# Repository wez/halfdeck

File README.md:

# Half Deck - Mk 5

This is my fifth keyboard design.  This repo will be updated as I get around to
expanding the data here.

This is a split keyboard in two halves.  One half has a microcontroller that
implements USB and communicates with the other half using a two-wire bus
protocol known as I2C.

The other half has an IO expander component that is connected to the keyboard
matrix and that can be queried over I2C.

A TRRS (Tip-Ring-Ring-Sleeve) cable is used to connect the two halves; this is
a 4-wire cable that carries the power and I2C signals to the IO expander.

## Firmware

You can find example firmware for an atmega32u4 based Feather board here:
https://github.com/wez/qmk_firmware/tree/flutterby-rebased/keyboards/halfdeck

## Before you begin

The PCBs are double sided so that the same design can be used to build either
the RHS or the LHS of the keyboard.  Make sure you read through this doc and
understand where you're going to place the components before you cut or solder
anything, as it can be difficult to undo those actions.

If you are using a plate with your keyboard (eg: the top acrylic plate with the key
switch holes), keep in mind that you can't solder in any of the switches until
you have the plate as the switches effectively bolt the plate to the PCB.
If your plate material is thicker than ~1.6mm then it won't clip into the small
lugs on the switches and you may need to add some M3 spacers to raise the plate
up to the appropriate height; depending on how you flush you solder your diodes
that may not be required.

The labels for the controller and IO multiplexer are biased towards right
handed users, or rather, assume that the touchpad be located on the RHS.  If
you want to place it on the LHS you will need to swap the multiplexer and the
controller.  This should be straightforward, but will require attaching those
components upside-down.  Pay careful attention to the labels on the pins to
ensure that you have things placed correctly!

## Assembly - Left Hand

The top of the PCB faces up for the Left Hand.  You'll know you've got it facing the
correct direction because it has a graphic showing a left hand in the bottom left
corner, as well as some version information down there.

You will place the key switches on this side of the board for the left hand but
solder them in on the other side.

If you are right handed and also want to connect a touch pad, you will connect
the SX1509 on this half.

If you are left handed and also want to connect a touch pad, you will connect
the controller and the touch pad on this half.

### I2C Jumper configuration

On the top edge of the PCB there is a little notch where the TRRS connector
will be fitted.  To the right of that area is a pair of solder jumpers labelled
`JP1` and `JP2`.  These are present to allow setting up the same PCB for either
left or right handed usage and control which pins of the TRRS connector are
connected to the power and ground lines.

Each jumper consists of three rectangles.  The middle of the three needs to
be bridged to *either* the left or the right pad using either excess solder
or a short section snipped off of one of the diode legs.  Controlling excess
solder can be difficult, so I would suggest using a diode leg trimmed to size
if you're not confident, or you don't have a solder sucker on hand to undo.

* `JP1` must be bridged to `3V3`
* `JP2` must be bridged to `GND`

It's not the end of the world if you mix this up, so long as each jumper either
goes to `GND` or `3V3`.  They must not both be set to the same thing or you
risk damaging your electronics.

This image shows the jumpers for the LHS:

## Assembly - Right Hand

The bottom of the PCB faces up for the Right Hand.  You'll see a graphic
showing a right hand in the bottom right corner of the PCB.

You will place the key switches on this side of the board for the right hand
but solder them in on the other side.

If you are right handed and also want to connect a touch pad, you will connect
the controller and the touch pad on this half.

If you are left handed and also want to connect a touch pad, you will connect
the SX1509 on this half.

### I2C Jumper configuration

Similar to the note on the Left Hand, but the Right Hand absolutely must have
the opposite settings to the Left Hand!

* `JP1` must be bridged to `GND`
* `JP2` must be bridged to `3V3`

While the PCB is mostly reversible, the jumper blocks are only present on
one side of the board, so you need to flip it over to configure them.

This image shows the jumpers for the HHS:

## Errata

The first batch of these boards have a minor issue with the `SCL` line; due to
a typo it isn't actually connected to the TRRS jack.  You will need to bridge
the misnamed `SDL` pads to the `SCL` pads on each side.

### Patching the RHS

### Patching the LHS

## Recommended Order of Assembly

1. Diodes
2. The TRRS connectors
3. Jumpers (I2C and the Errata section above)
4. Header strip for the controller/expander
5. Key switches
6. Touchpad

## Diodes

The diodes are directional; they allow current to flow in a single direction.
Their purpose in the circuit is to prevent ghosting.  If you attach one in
the wrong direction it can be hard to debug and isolate if you don't have
a multimeter, so take care to make sure you've placed them correctly.

The diodes have a black line at one end.  The black line must be aligned with
the thick white line in the diode outline on the PCB.  The solder pad on that
side is square, which is another visual cue; think *black, thick, square*.

Bend the legs of the diode so that you form a slender `n` shape, with the diode
body at the top of the `n`.  The goal is to have the diode body lay flush against
the PCB within the outline on the pcb, so you want the legs to bend and fit the
holes at either end of the outline.

I'd suggest taking your time with the first one and perhaps solder that one
before placing the rest to make sure you understand how it will fit.  Make
sure that you have it oriented correctly before soldering!

To solder the diodes, the technique is important.  You're placing the diodes
on the side of the board facing up but you need to solder them on the back side
of the board.  I bend the legs to form a `V` shape to keep the diodes in place
when you flip the board over:

Once you've placed the diodes, check again to make sure that you have them
facing the right direction (*black, thick, square*) and solder them in.  You
want enough solder that you fill the hole with a nice shiny blob, and you want
it to be very slightly convex.

Be careful with the diode legs: you can easily prick yourself on the legs and
the human reflex to suddenly move away from the prick can be dangerous if one
of your hands is holding a hot soldering iron!

After soldering, double check the orientation of the diodes again: it's not
super easy to correct at this point, but it will get much harder if you
discover a problem later because the next step is to snip off the diode legs.

Use your angle/flush cutters for this; lay the edge of the cutters flush with
the board and snip off the leg where it comes through the hole.  Ideally you
want to trim it such that you're just left with a small convex mound of solder
around the hole.  I recommend holding the leg with one hand while you snip; the
picture below doesn't show this because I was holding the camera to take the
picture.  The reason for holding the leg while snipping is that it can jump off
your work surface and land on the floor.  If you're not diligent at tracking
and picking up the legs from the floor, it is easy for someone to stub/stab a
toe with a diode leg.  While they're not super sharp, they're small enough that
they can jab in a few millimeters and draw blood.

## TRRS Connectors

Attaching these is pretty straightforward; look for the little notch in the PCB
near the I2C jumpers.  The notch makes room for the circular opening in the
connector.  Place the legs of the component through the holes and solder on the
other side.

If you are using a plate with your keyboard, check to see whether you have enough
clearance to mount the connector on the switch side of the plate.  If you
have an acrylic plate than I suspect that there won't be enough clearance.
If you're using a 1.6mm plate then it looks like it might just fit.

In the pictures in this guide, I built without a plate and placed the connectors
on the top side of the PCB.

## Header Strip for Controller and Expander

I recommend using some header strip to mount these components.  The controller
comes with appropriately sized strip but you'll need to obtain some more header
to mount the IO expander.

Similar consideration as the TRRS connector: make sure that you have enough
clearance to place the components and your plate if you're using a plate.  You
may need to mount the components on the opposite side of the board to
accomodate your plate.   Note that you can also [buy short header
strip](https://www.adafruit.com/product/3002) for lower profile builds.

This image shows the header strip placement for the IO Expander:

When soldering the header be prepared: `GND` is attached to a larger ground
plane fill in that area of the board; there's large region of copper under the
surface coating and that means that it will soak up the heat from your iron and
be more difficult/take longer to solder than the surrounding pins. You may
notice that the PCB in that region is noticeably much hotter.  This is fine.

## Key Switches

These should also be pretty simple to place, especially if you ordered PCB
mounted switches.  The PCB mounted switches have a couple of extra legs to
ensure that the switch is correctly aligned in the PCB.  If you have plate
mounted switches, those lugs are not present because the plate is supposed to
orient and align the switches.

If you're using plate mounted switches on the PCB and are not using a plate
you will need to take extra care to ensure that the switches mount square
and consistently, otherwise your keycaps will be misaligned.

Press the key switches into the mounting holes; make sure that the metal legs
of the switch poke through the other side.  If you don't see a leg poking
through it means that the leg is most likely folded flat; remove the switch and
straighten the leg and try again.

Make sure that the switches are pushed in snugly and that the switches are
flush with the PCB, otherwise your keycaps will be misaligned.  You may hear or
feel a click when the switch is well placed.

I tend to place all of the switches at once, then flip the board over and
solder them in.  Before you solder, make sure that none of the switches shifted
during the flip.  In my test build the tolerance on the hole was good and the
switches were held in just fine, but depending on your switches you may find
that one or two of them are a little loose and need to be re-seated.

## Touchpad

I tried two different touchpad models.  The one I'm most happy with is the
Azoteq TPS43-201A-S, which is a 43mm approximately-square touchpad which
connects to the I2C bus on this keyboard.  When I designed the board I
though I was going to use a different touchpad that was connected via SPI,
so the mounting area on the board breaks out the SPI pins but not the I2C
pins.  That means that connecting the touchpad requires a couple of bridging
wires to connect across the backside of the pcb.

The touchpad is shipped with a removable 3M adhesive pad on the touch surface;
**keep this attached to the touchpad** (well, you can peel back a corner and
take a peek at the sensor grid if you like).  The purpose of this is to ensure
that you have no air gap between the capacitive touch grid on the touchpad
surface and the touch surface.  The 3M label makes a reasonable touch surface,
but you may want to consider placing your own more permanent and aestheticly
pleasing surface in its place.  The datasheet recommends a surface that is no
more than 3mm thick, and it should be something that doesn't interfere with the
capacitive field.

### Touchpad Wiring

Prepare your bridging wires; you'll need 3 that are long and two that are relatively
short.  You'll want to give yourself a little slack but not so much that
the wires crowd out the underside of your board.

Here's a picture of the wiring on the reverse of the PCB so that you can
visualize this a little better; the slack allows popping off the case in
the event that you need to get inside the board and clean it.

The touchpad itself provides solderable pads that are just perfect for
our needs:

The pads are connected to the PCB via the briding wires:

| Touchpad | PCB |
| -------- | --- |
| SDA      | SDA - on the header block at the top of the board |
| SCL      | SCL - on the first rev of the PCB this is mislabeled as SDL on the header block at the top of the board |
| 3V3      | 3V3 - in the header block in the circle at the bottom of the board |
| GND      | GND - in the header block in the circle at the bottom of the board |
| RST      | Not connected |
| RDY      | ~INT - the interrupt pin behind the microcontroller |

### Orientation of the touchpad

The top edge of the touchpad has a small notch.  When the touchpad is placed
on the board, the solder pads for the connections listed in the table above
will be in the bottom right of the touchpad if you look down from the top
surface of the touch pad.

While you're soldering you'll have it facing up the other way and so those pads
will be in the bottom left of the underside of the touchpad.

### Mounting the touchpad

I've only made this work when integrating with the 3D printed flavor of the case.
You'll need the [touchpad_stand](case/touchpad_stand.stl) to raise the pad up to
the level of the case.  There is an open side in the touchpad stand that is intended
to allow your wiring to pass through; the idea is that you don't want to solder your
wires into the stand as you won't be able to remove it without de-soldering.

## Case

In the [case](case) directory you'll find a number of files to use for the case.  You
have a couple of options:

### 2D laser cut sandwich style case

This is the simplest case design, but because it is 2D doesn't have a story for (literally)
supporting the touchpad.  There are no sides to the case and the idea is that
you assemble it using some M3 standoffs/spacers and nuts and bolts.  There are a number
of SVG files in the repo that can be used to assemble a case.  For example, you can
take [this one](case/half-deck-case-bottom-and-switch-plate-no-touch-pad-ponoko-p2.svg)
to [Ponoko](https://www.ponoko.com/) and select you preferred color of acrylic P2 material.

### 3D printed case (work in progress)

> Pictured above: a debug version of the case with partially exposed controller.
> The case files below are fully enclosed but I don't have a real print of that
> to show at this time.

This one is your best option when using a touchpad.  There are a couple of parts to print in
the current iteration.  These are for a right handed build including a touchpad.  You can
mirror the parts if you want a left handed build with a touchpad, or just mirror the left
half if you want a right half with no touchpad:

 * [left half](case/left-case.stl)
 * [right_half](case/right-case.stl)
 * [touchpad_stand](case/touchpad_stand.stl)
 * Currently missing: bottom cover.  It's not strictly needed as the case has a lip
   with sufficient clearance, but you can extrude [case-bottom.svg](case/case-bottom.svg)
   and print that or just laser cut it from some other material if you really need
   something.

You'll need some M3 bolts to attach the PCB to the case and something like these
[heat-set embedment nuts](https://www.amazon.com/gp/product/B01IYWTCWW)
to provide threads that you can screw the bolts into.  Check out 
[this page](https://www.3dhubs.com/knowledge-base/how-assemble-3d-printed-parts-threaded-fasteners)
for more information.

If you don't have a 3D printer you can upload these files to somewhere like
[3D Hubs](https://www.3dhubs.com/) and have them printed for you at a cost of
around $50 for one set, plus shipping.

If you do have a 3D printer but it isn't large enough to print these models, you'll
find a set of `sliced_case` files in this repo that are divided into quarters that
are printable in a printer with a 140 cubic mm volume.  These are cut in such a way
that the pieces lock together when mounted on the PCB.

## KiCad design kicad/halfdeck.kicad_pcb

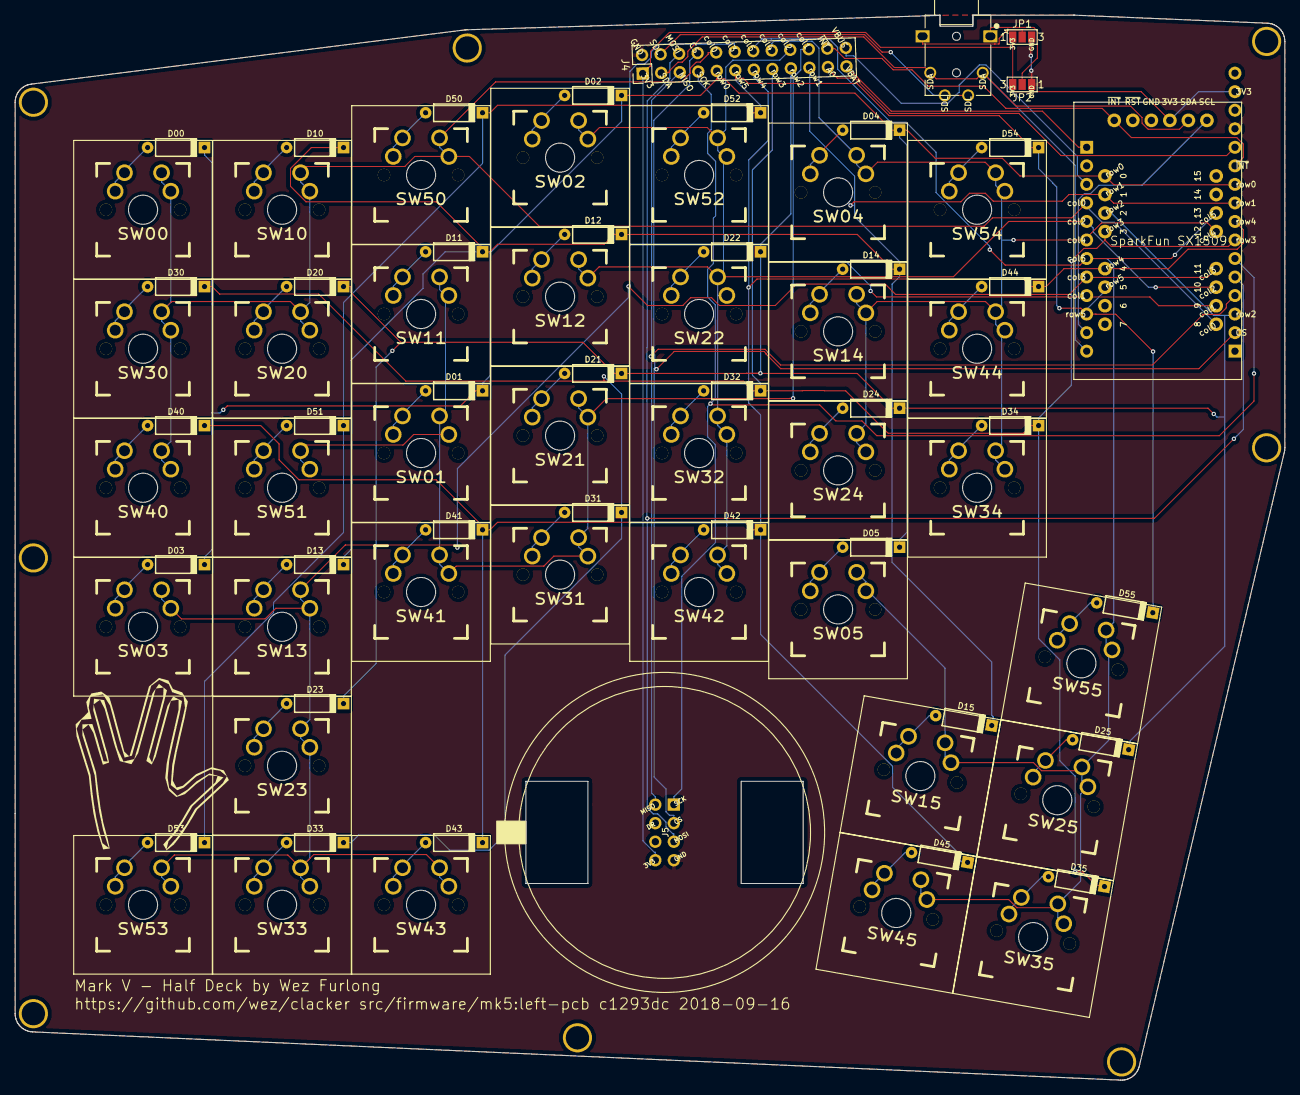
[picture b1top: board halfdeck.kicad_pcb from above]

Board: 2 copper layers, 174.0 x 145.9 mm, 89 parts (1 on the bottom side), 63 nets.

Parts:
CP0: VAL**; CP0
CP1: VAL**; CP1
CP2: VAL**; CP2
CP3: VAL**; CP3
CP4: VAL**; CP4
CP5: VAL**; CP5
CP6: VAL**; CP6
CP7: VAL**; CP7
D00: D; D00
D01: D; D01
D02: D; D02
D03: D; D03
D04: D; D04
D05: D; D05
D10: D; D10
D11: D; D11
D12: D; D12
D13: D; D13
D14: D; D14
D15: D; D15
D20: D; D20
D21: D; D21
D22: D; D22
D23: D; D23
D24: D; D24
D25: D; D25
D30: D; D30
D31: D; D31
D32: D; D32
D33: D; D33
D34: D; D34
D35: D; D35
D40: D; D40
D41: D; D41
D42: D; D42
D43: D; D43
D44: D; D44
D45: D; D45
D50: D; D50
D51: D; D51
D52: D; D52
D53: D; D53
D54: D; D54
D55: D; D55
J1: VAL**; J1
J4: Pin_Header_Straight_2x12_Pitch2.54mm; J4
J5: VAL**; J5
JP1: SolderJumper-3_P1.3mm_Open_Pad1.0x1.5mm_NumberLab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; JP1
JP2: SolderJumper-3_P1.3mm_Open_Pad1.0x1.5mm_NumberLab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; JP2
SW00: SW00
SW01: SW01
SW02: SW02
SW03: SW03
SW04: SW04
SW05: SW05
SW10: SW10
SW11: SW11
SW12: SW12
SW13: SW13
SW14: SW14
SW15: SW15
SW20: SW20
SW21: SW21
SW22: SW22
SW23: SW23
SW24: SW24
SW25: SW25
SW30: SW30
SW31: SW31
SW32: SW32
SW33: SW33
SW34: SW34
SW35: SW35
SW40: SW40
SW41: SW41
SW42: SW42
SW43: SW43
SW44: SW44
SW45: SW45
SW50: SW50
SW51: SW51
SW52: SW52
SW53: SW53
SW54: SW54
SW55: SW55
U1: FEATHER; U1
U2: SparkFun SX1509; U2
X9: G***; X9
X10: G***; X10

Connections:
3V3: J4.1, J5.8, JP1.1, JP2.3, U1.+3V3, U2.3V3
A0: J4.21, U1.A0
CS: J4.8, J5.3, U1.D1
GND: J4.2, J5.7, JP1.3, JP2.1, U1.GND, U2.GND
MISO: J4.5, J5.2, U1.MISO
MOSI: J4.6, J5.5, U1.MOSI
unnamed: J1.R2, JP1.2
unnamed: J1.S, JP2.2
unnamed: D00.2, SW00.2, SW00.2a
unnamed: D01.2, SW01.2, SW01.2a
unnamed: D02.2, SW02.2, SW02.2a
unnamed: D03.2, SW03.2, SW03.2a
unnamed: D04.2, SW04.2, SW04.2a
unnamed: D05.2, SW05.2, SW05.2a
unnamed: D10.2, SW10.2, SW10.2a
unnamed: D11.2, SW11.2, SW11.2a
unnamed: D12.2, SW12.2, SW12.2a
unnamed: D13.2, SW13.2, SW13.2a
unnamed: D14.2, SW14.2, SW14.2a
unnamed: D15.2, SW15.2, SW15.2a
unnamed: D20.2, SW20.2, SW20.2a
unnamed: D21.2, SW21.2, SW21.2a
unnamed: D22.2, SW22.2, SW22.2a
unnamed: D23.2, SW23.2, SW23.2a
unnamed: D24.2, SW24.2, SW24.2a
unnamed: D25.2, SW25.2, SW25.2a
unnamed: D30.2, SW30.2, SW30.2a
unnamed: D31.2, SW31.2, SW31.2a
unnamed: D32.2, SW32.2, SW32.2a
unnamed: D33.2, SW33.2, SW33.2a
unnamed: D34.2, SW34.2, SW34.2a
unnamed: D35.2, SW35.2, SW35.2a
unnamed: D40.2, SW40.2, SW40.2a
unnamed: D41.2, SW41.2, SW41.2a
unnamed: D42.2, SW42.2, SW42.2a
unnamed: D43.2, SW43.2, SW43.2a
unnamed: D44.2, SW44.2, SW44.2a
unnamed: D45.2, SW45.2, SW45.2a
unnamed: D50.2, SW50.2, SW50.2a
unnamed: D51.2, SW51.2, SW51.2a
unnamed: D52.2, SW52.2, SW52.2a
unnamed: D53.2, SW53.2, SW53.2a
unnamed: D54.2, SW54.2, SW54.2a
unnamed: D55.2, SW55.2, SW55.2a
SCK: J4.7, J5.1, U1.SCK
SCL: U1.SCL, U2.SCL
SDA: J1.T, J1.Talt, J4.3, U1.SDA, U2.SDA
SDL: J1.R1, J1.R1alt, J4.4
VBAT: J4.23, U1.VBAT
VBUS: J4.24, U1.VBUS
col0: J4.10, SW00.1, SW00.1a, SW10.1, SW10.1a, SW20.1, SW20.1a, SW30.1, SW30.1a, SW40.1, SW40.1a, SW50.1, SW50.1a, U1.D13, U2.8
col1: J4.20, SW01.1, SW01.1a, SW11.1, SW11.1a, SW21.1, SW21.1a, SW31.1, SW31.1a, SW41.1, SW41.1a, SW51.1, SW51.1a, U1.D6, U2.9
col2: J4.18, SW02.1, SW02.1a, SW12.1, SW12.1a, SW22.1, SW22.1a, SW32.1, SW32.1a, SW42.1, SW42.1a, SW52.1, SW52.1a, U1.D12, U2.10
col3: J4.12, SW03.1, SW03.1a, SW13.1, SW13.1a, SW23.1, SW23.1a, SW33.1, SW33.1a, SW43.1, SW43.1a, SW53.1, SW53.1a, U1.D9, U2.11
col4: J4.16, SW04.1, SW04.1a, SW14.1, SW14.1a, SW24.1, SW24.1a, SW34.1, SW34.1a, SW44.1, SW44.1a, SW54.1, SW54.1a, U1.D11, U2.12
col5: J4.14, SW05.1, SW05.1a, SW15.1, SW15.1a, SW25.1, SW25.1a, SW35.1, SW35.1a, SW45.1, SW45.1a, SW55.1, SW55.1a, U1.D10, U2.13
row0: D00.1, D01.1, D02.1, D03.1, D04.1, D05.1, J4.9, U1.A2, U2.0
row1: D10.1, D11.1, D12.1, D13.1, D14.1, D15.1, J4.19, U1.A3, U2.1
row2: D20.1, D21.1, D22.1, D23.1, D24.1, D25.1, J4.17, U1.D0, U2.2
row3: D30.1, D31.1, D32.1, D33.1, D34.1, D35.1, J4.15, U1.A5, U2.3
row4: D40.1, D41.1, D42.1, D43.1, D44.1, D45.1, J4.13, U1.A4, U2.4
row5: D50.1, D51.1, D52.1, D53.1, D54.1, D55.1, J4.11, U1.D5, U2.5
~INT: J4.22, U1.A1, U2.~INT

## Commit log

2018-09-17 Add initial designs as submitted for manufacture
2018-09-17 add generated case files
2018-09-17 add pcb render
2018-09-17 add note on jumper configuration before I forget
2018-09-29 add some case design files for ponoko
2018-09-29 add some build notes
2018-09-29 add more detail
2018-09-29 add picture of an assembled board
2018-09-29 add note about ground plane, link to firmware
2018-11-14 Add mounting assembly for trackpad
2018-12-02 fix whitespace
2018-12-02 Add a little bit of explanation about the touchpad.
    Include the work in progress case files.
2018-12-02 fix filenames for touchpad stand
2018-12-02 add some more information about the case
2018-12-02 use the fully enclosed RHS case variant
2018-12-02 add case picture
